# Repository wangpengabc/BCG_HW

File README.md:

<<<<<<< HEAD
# BCG_HW
=======
# BCG_HW
piezo_V1.0 : base electric collector
>>>>>>> f33a43ac3dc7ae816907e558396766c5b4fa1197
nihao

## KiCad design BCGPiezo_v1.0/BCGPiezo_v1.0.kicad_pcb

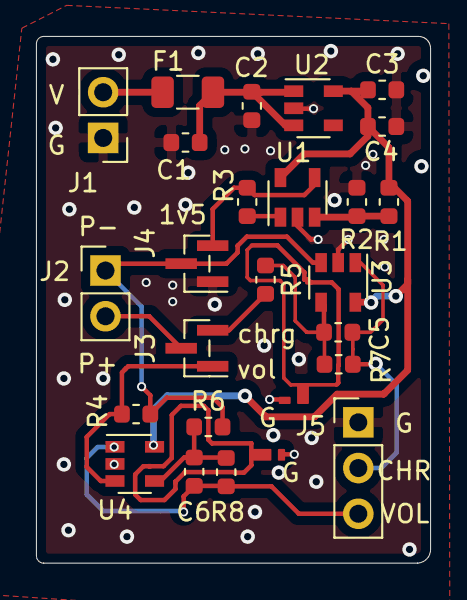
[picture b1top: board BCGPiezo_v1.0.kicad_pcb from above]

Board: 2 copper layers, 21.9 x 29.3 mm, 24 parts (0 on the bottom side), 15 nets.

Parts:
C1, C2, C3: 10uF; C_0603_1608Metric
C4: 0.01uF; C_0603_1608Metric
C5, C6: 10pF; C_0603_1608Metric
F1: Fuse; Fuse_1206_3216Metric
J1, J2: Conn_01x02; PinHeader_1x02_P2.54mm_Vertical
J3, J4: Conn_01x03; PinHeader_1x03_P1.00mm_Vertical_SMD_Pin1Left
J5: Conn_01x03; PinHeader_1x03_P2.54mm_Vertical
R1, R2, R3, R6, R8: 10k; R_0603_1608Metric
R4, R7: 1G; R_0603_1608Metric
R5: R; R_0603_1608Metric
U1, U3, U4: TLV2771; SOT-23-5
U2: LD6836_SOT23; SOT-23-5

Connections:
+1V5: J4.3, R3.1, U1.4
+3V3: C3.1, C4.1, R1.2, U1.5, U2.5, U3.5, U4.5
+BATT: C1.1, C2.1, F1.1, U2.1, U2.3
/charge_out: C5.1, J5.2, R7.1, U3.1
/opmP: J2.1, J4.2, R4.1, R6.2, U3.3
/piezoP: J2.2, J3.2
/vol_mode: J3.1, R4.2, U4.3
/vol_out: C6.1, J5.3, R8.1, U4.1
GND: C1.2, C2.2, C3.2, C4.2, J1.1, J4.1, J5.1, R2.1, U1.2, U2.2, U3.2, U4.2
unnamed: C5.2, R5.1, R7.2, U3.4
unnamed: C6.2, R6.1, R8.2, U4.4
unnamed: F1.2, J1.2
unnamed: J3.3, R5.2
unnamed: R1.1, R2.2, U1.3
unnamed: R3.2, U1.1

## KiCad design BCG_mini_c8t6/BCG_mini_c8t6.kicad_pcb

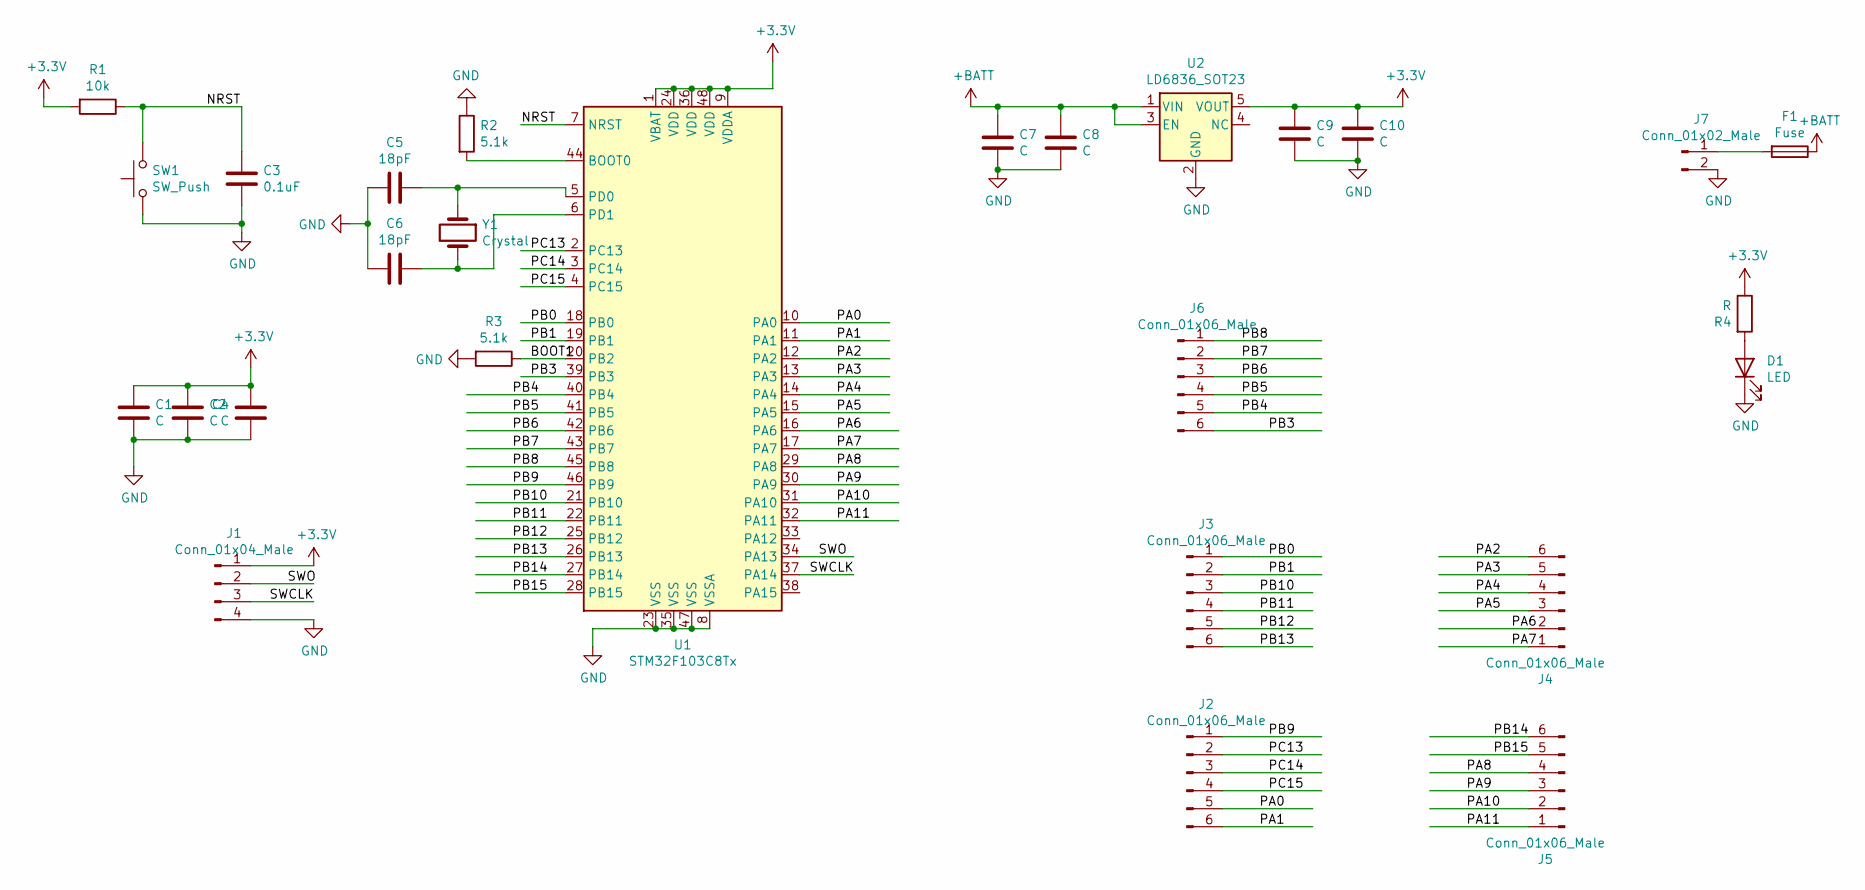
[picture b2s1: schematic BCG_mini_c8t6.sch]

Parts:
C1, C2, C4, C7, C8, C9, C10: C; C_0603_1608Metric
C3: 0.1uF; C_0603_1608Metric
C5, C6: 18pF; C_0603_1608Metric
D1: LED; LED_0603_1608Metric
F1: Fuse; Fuse_0805_2012Metric
J1: Conn_01x04_Male; PinHeader_1x04_P2.54mm_Vertical
J2, J3, J4, J5, J6: Conn_01x06_Male; PinHeader_1x06_P2.54mm_Vertical
J7: Conn_01x02_Male; PinHeader_1x02_P2.54mm_Vertical
R1: 10k; R_0603_1608Metric
R2, R3: 5.1k; R_0603_1608Metric
R4: R; R_0603_1608Metric
SW1: SW_Push; SW_SPST_EVQPE1
U1: STM32F103C8Tx; LQFP-48_7x7mm_P0.5mm
U2: LD6836_SOT23; SOT-23-5
Y1: Crystal; Crystal_SMD_5032-2Pin_5.0x3.2mm

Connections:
+3V3: C1.1, C2.1, C4.2, C9.2, C10.2, J1.1, R1.2, R4.1, U1.1 (VBAT), U1.9 (VDDA), U1.24 (VDD), U1.36 (VDD), U1.48 (VDD), U2.5 (VOUT)
+BATT: C7.2, C8.2, F1.1, U2.1 (VIN), U2.3 (EN)
/BOOT1: R3.1, U1.20 (PB2)
/NRST: C3.1, R1.1, SW1.2, U1.7 (NRST)
/PA0: J2.5, U1.10 (PA0)
/PA1: J2.6, U1.11 (PA1)
/PA2: J4.6, U1.12 (PA2)
/PA3: J4.5, U1.13 (PA3)
/PA4: J4.4, U1.14 (PA4)
/PA5: J4.3, U1.15 (PA5)
/PA6: J4.2, U1.16 (PA6)
/PA7: J4.1, U1.17 (PA7)
/PA8: J5.4, U1.29 (PA8)
/PA9: J5.3, U1.30 (PA9)
/PA10: J5.2, U1.31 (PA10)
/PA11: J5.1, U1.32 (PA11)
/PB0: J3.1, U1.18 (PB0)
/PB1: J3.2, U1.19 (PB1)
/PB3: J6.6, U1.39 (PB3)
/PB4: J6.5, U1.40 (PB4)
/PB5: J6.4, U1.41 (PB5)
/PB6: J6.3, U1.42 (PB6)
/PB7: J6.2, U1.43 (PB7)
/PB8: J6.1, U1.45 (PB8)
/PB9: J2.1, U1.46 (PB9)
/PB10: J3.3, U1.21 (PB10)
/PB11: J3.4, U1.22 (PB11)
/PB12: J3.5, U1.25 (PB12)
/PB13: J3.6, U1.26 (PB13)
/PB14: J5.6, U1.27 (PB14)
/PB15: J5.5, U1.28 (PB15)
/PC13: J2.2, U1.2 (PC13)
/PC14: J2.3, U1.3 (PC14)
/PC15: J2.4, U1.4 (PC15)
/SWCLK: J1.3, U1.37 (PA14)
/SWO: J1.2, U1.34 (PA13)
GND: C1.2, C2.2, C3.2, C4.1, C5.2, C6.2, C7.1, C8.1, C9.1, C10.1, D1.1 (K), J1.4, J7.2, R2.1, R3.2, SW1.1, U1.8 (VSSA), U1.23 (VSS), U1.35 (VSS), U1.47 (VSS), U2.2 (GND)
unnamed: C5.1, U1.5 (PD0), Y1.1
unnamed: C6.1, U1.6 (PD1), Y1.2
unnamed: D1.2 (A), R4.2
unnamed: F1.2, J7.1
unnamed: R2.2, U1.44 (BOOT0)

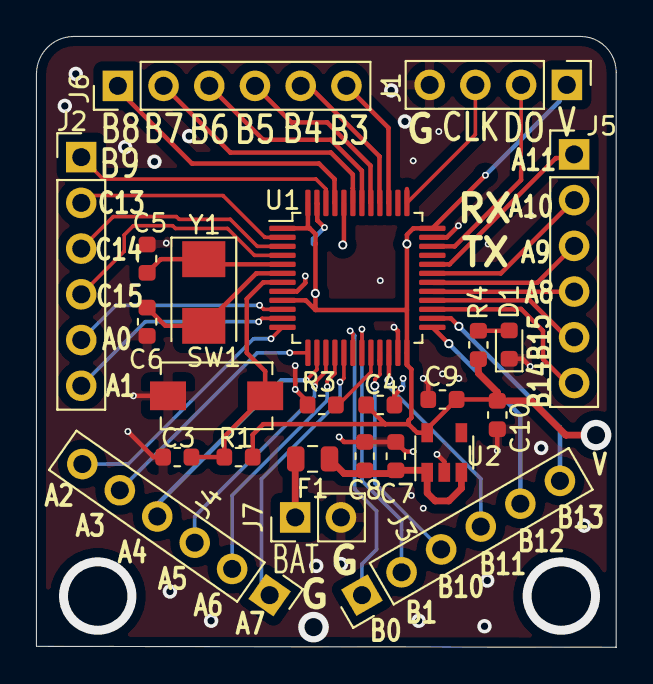
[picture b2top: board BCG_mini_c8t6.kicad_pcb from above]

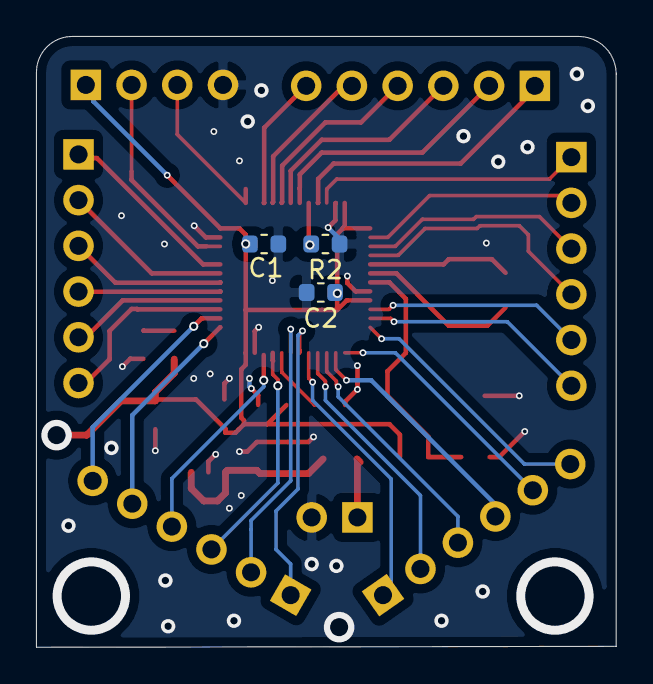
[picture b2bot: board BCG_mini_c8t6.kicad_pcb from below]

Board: 2 copper layers, 32.2 x 33.9 mm, 27 parts (3 on the bottom side), 42 nets.

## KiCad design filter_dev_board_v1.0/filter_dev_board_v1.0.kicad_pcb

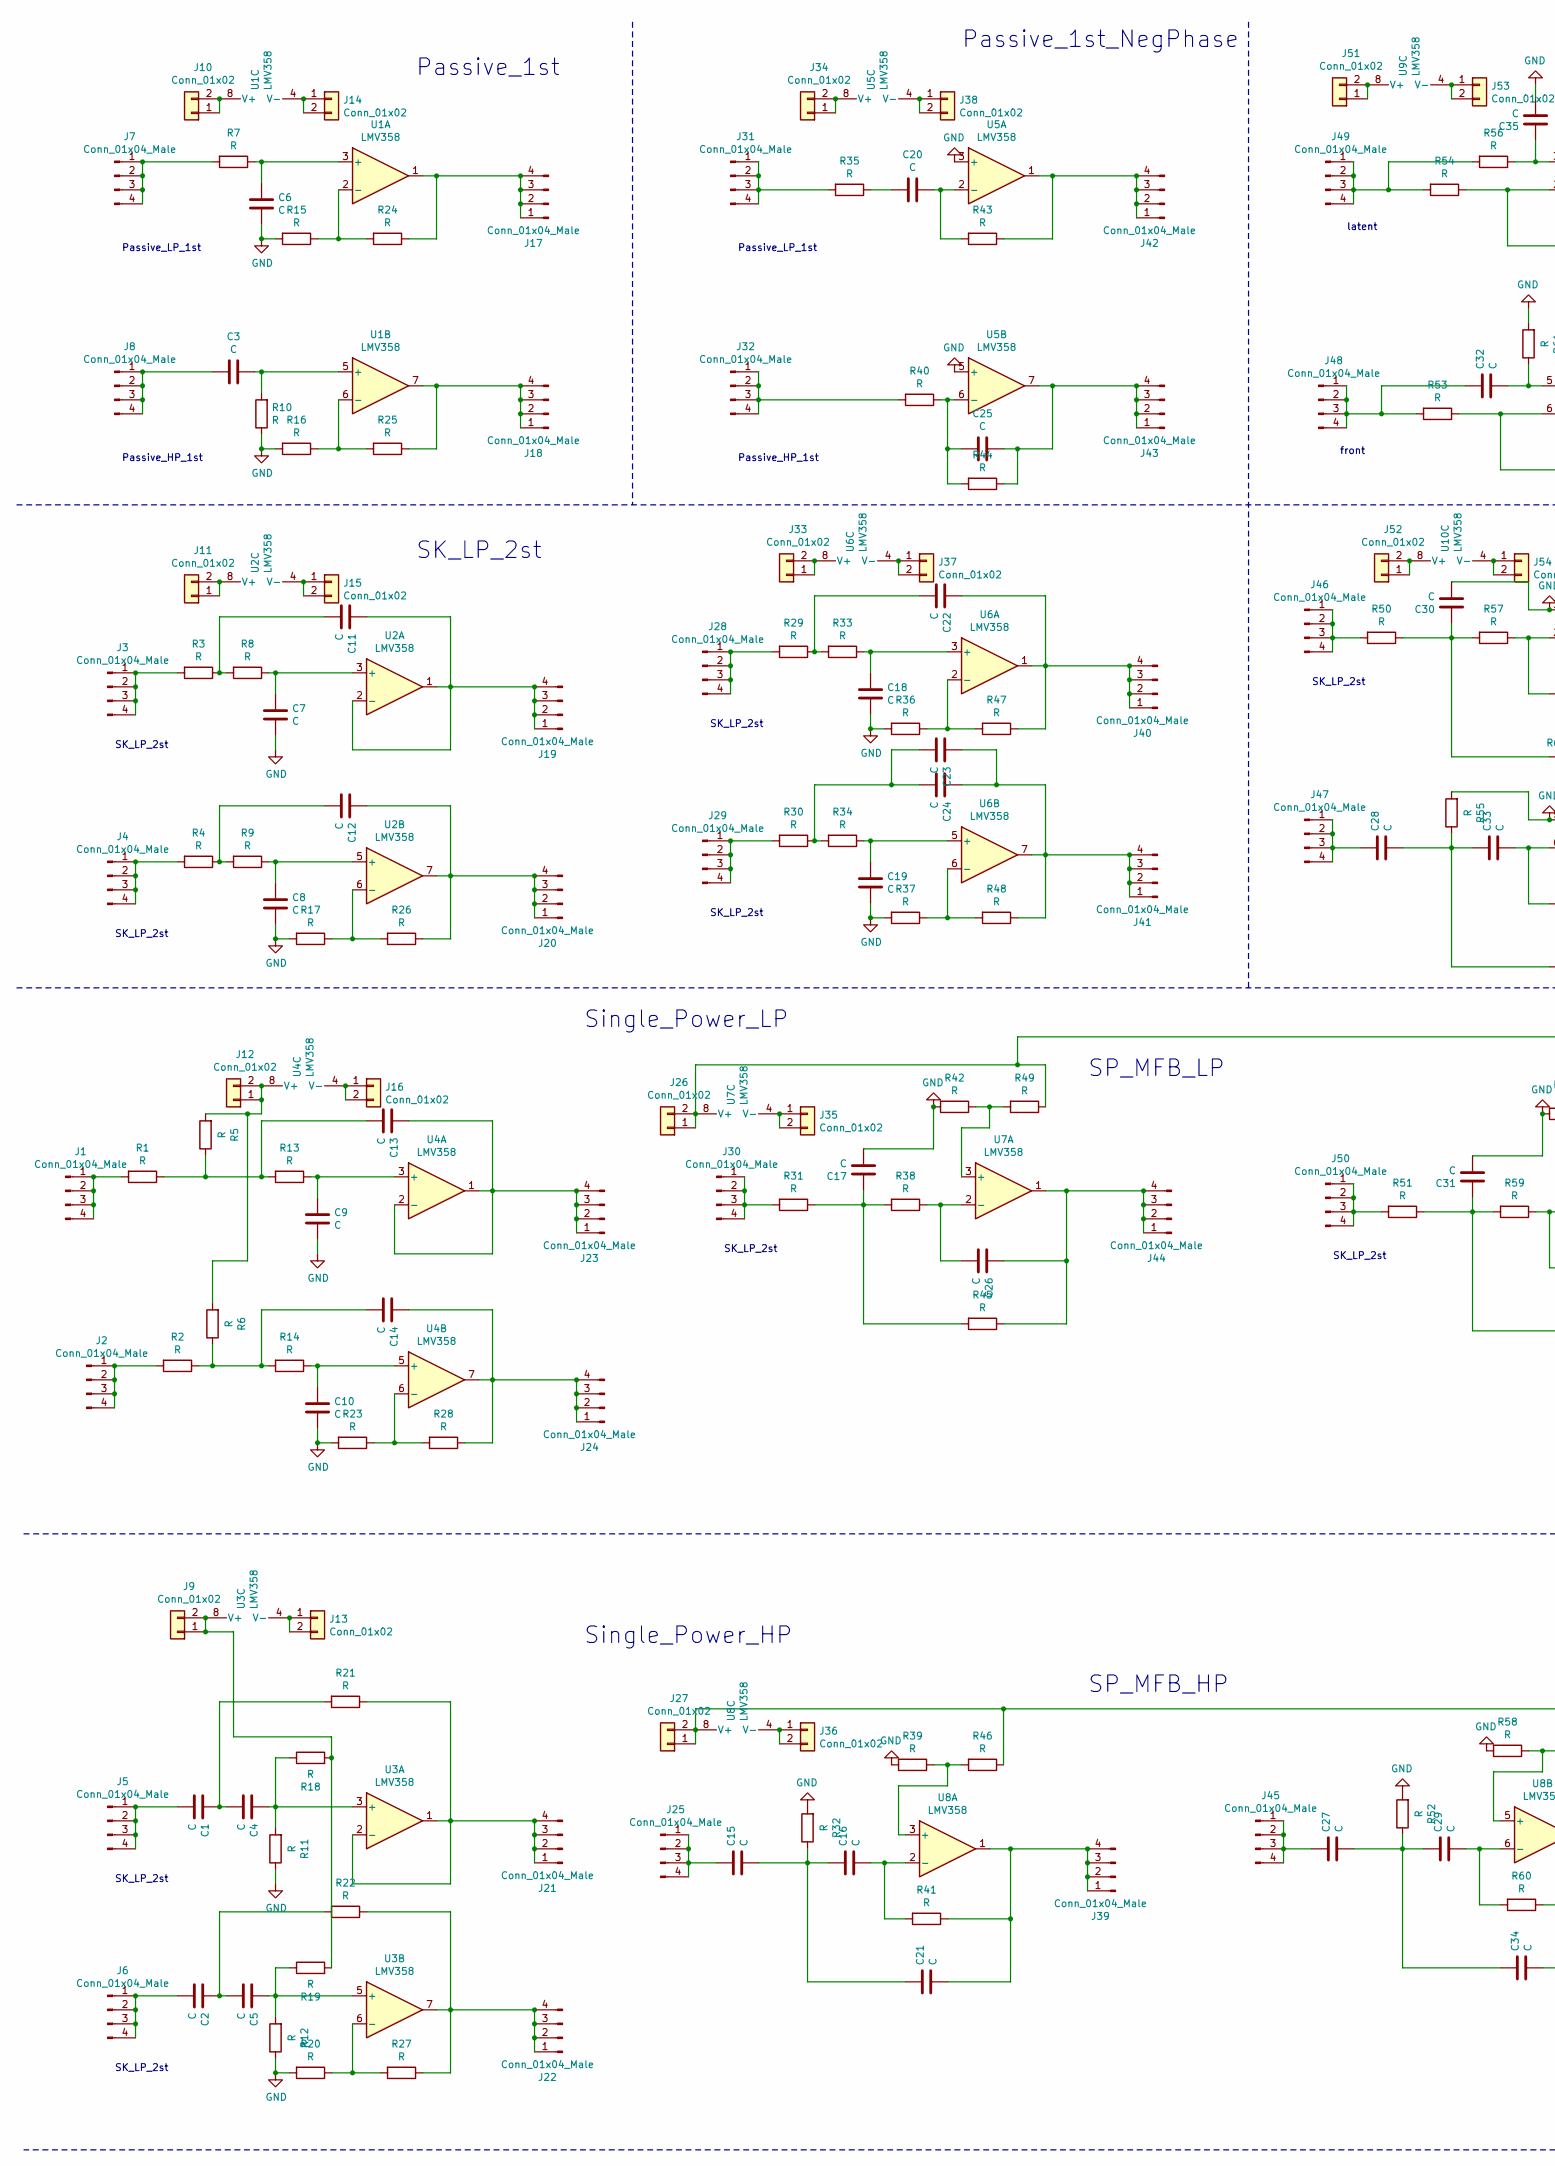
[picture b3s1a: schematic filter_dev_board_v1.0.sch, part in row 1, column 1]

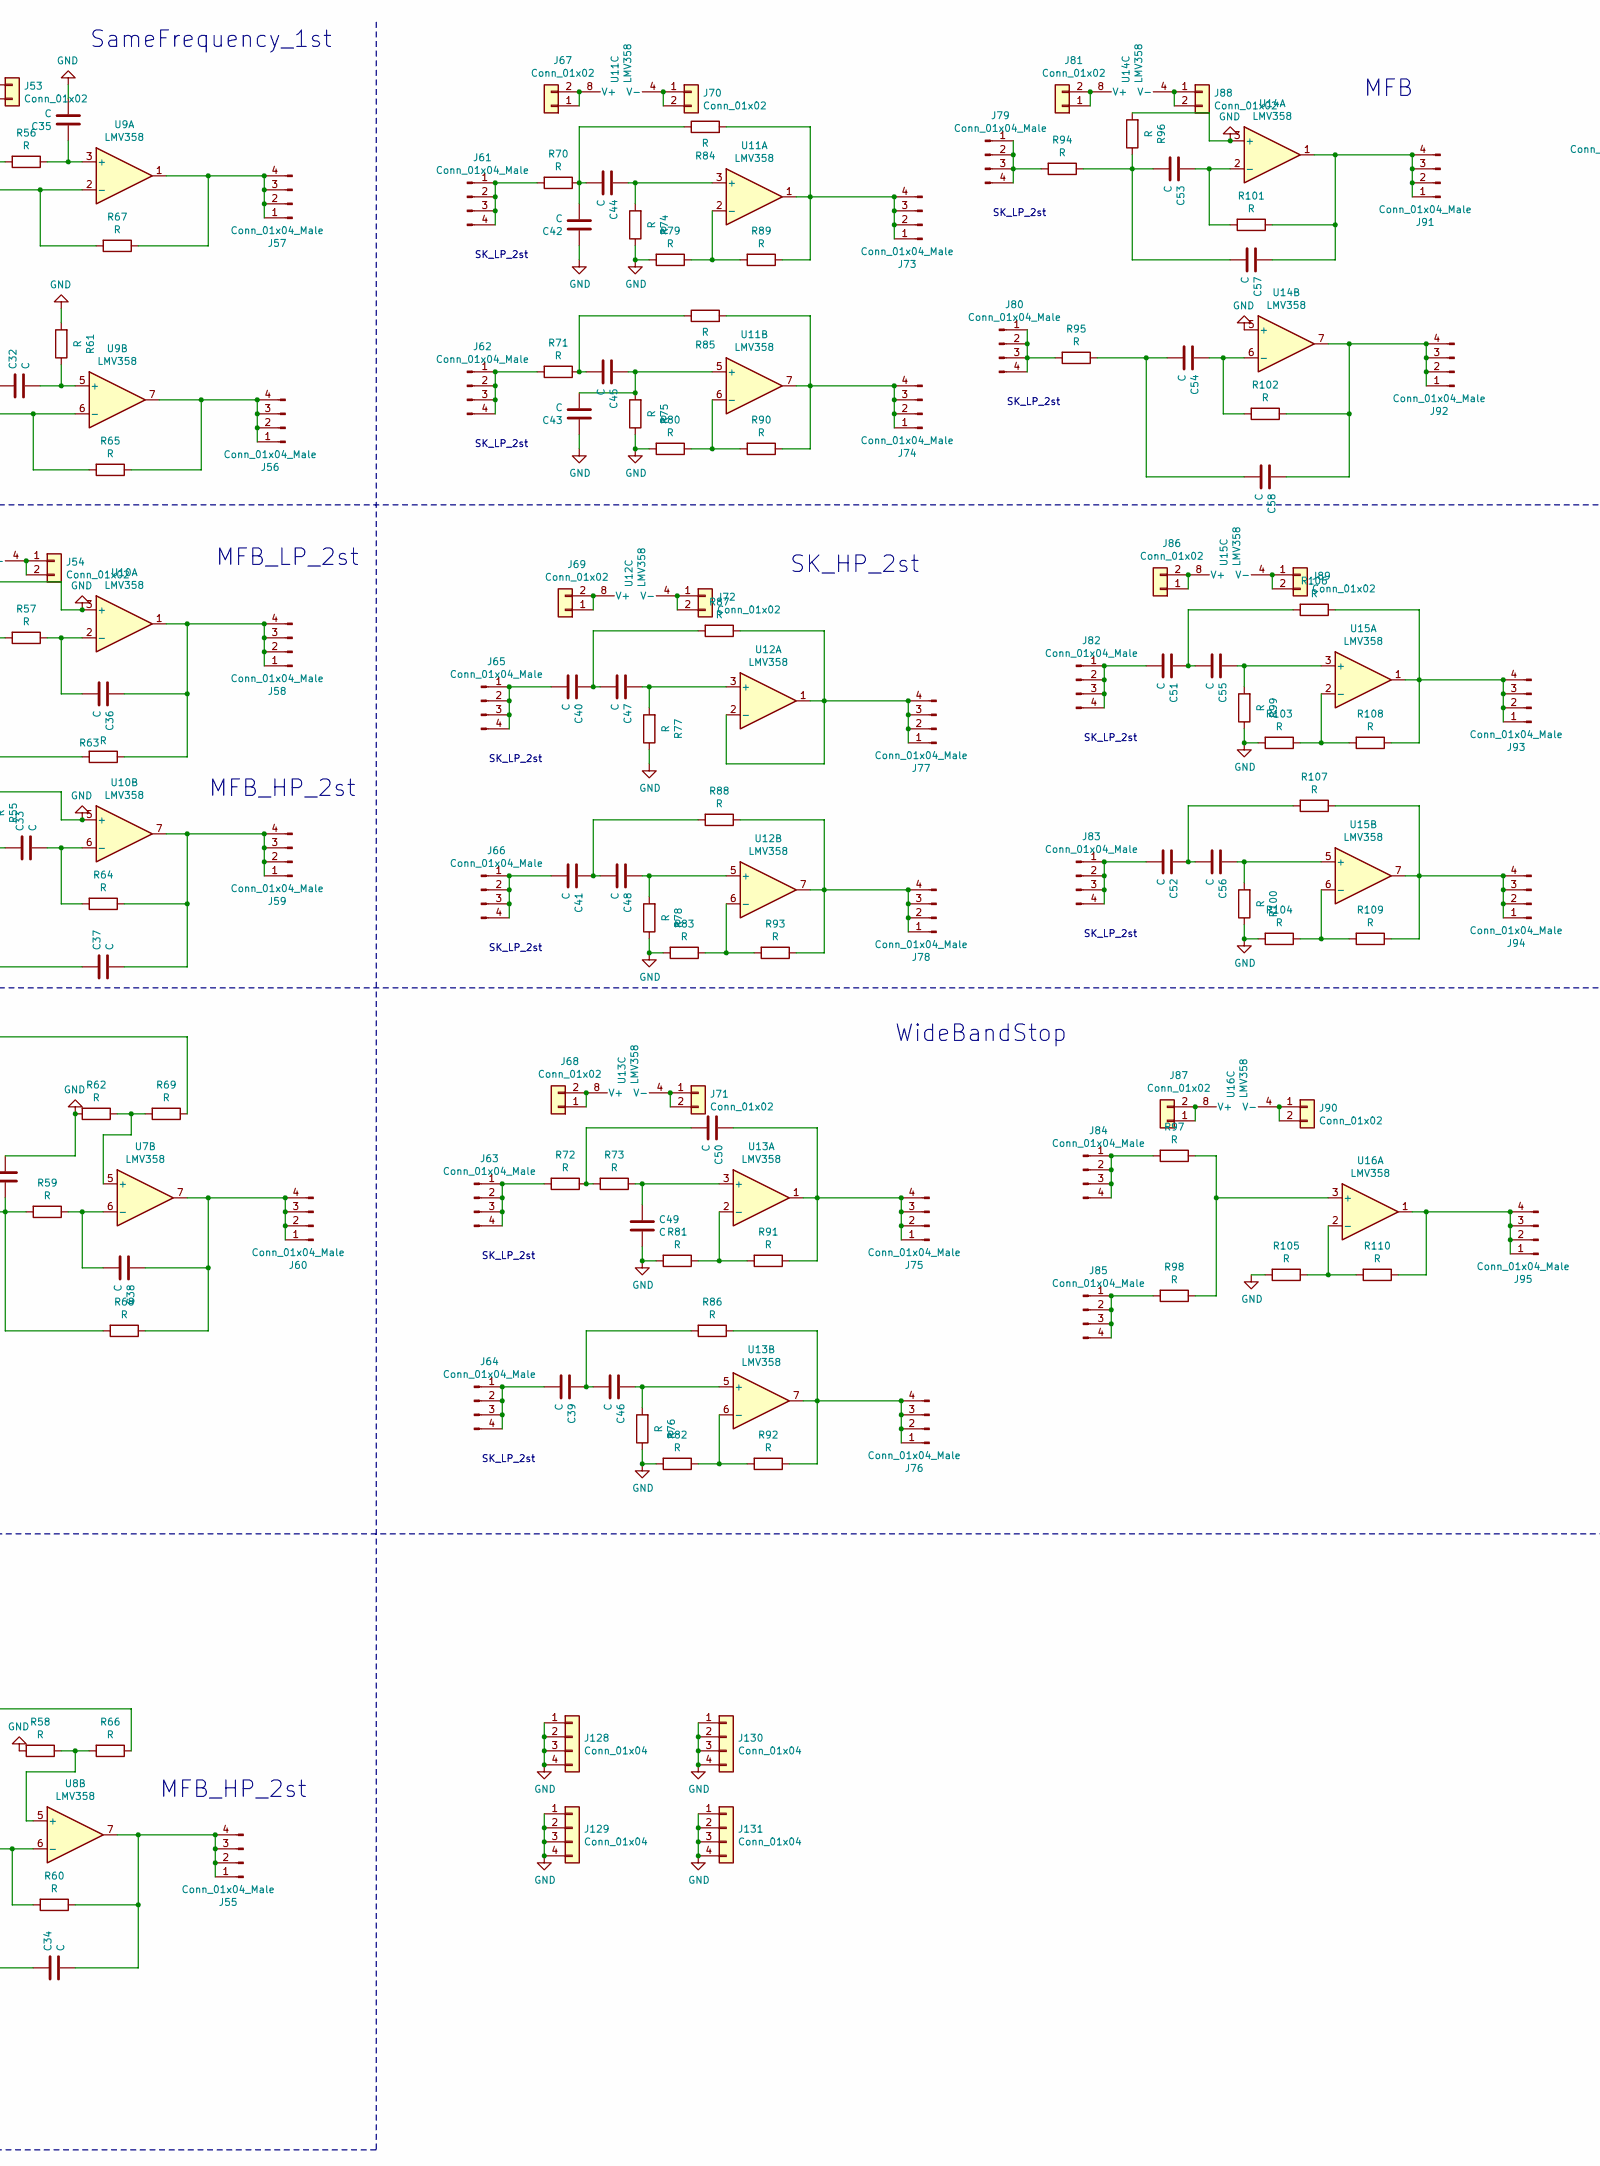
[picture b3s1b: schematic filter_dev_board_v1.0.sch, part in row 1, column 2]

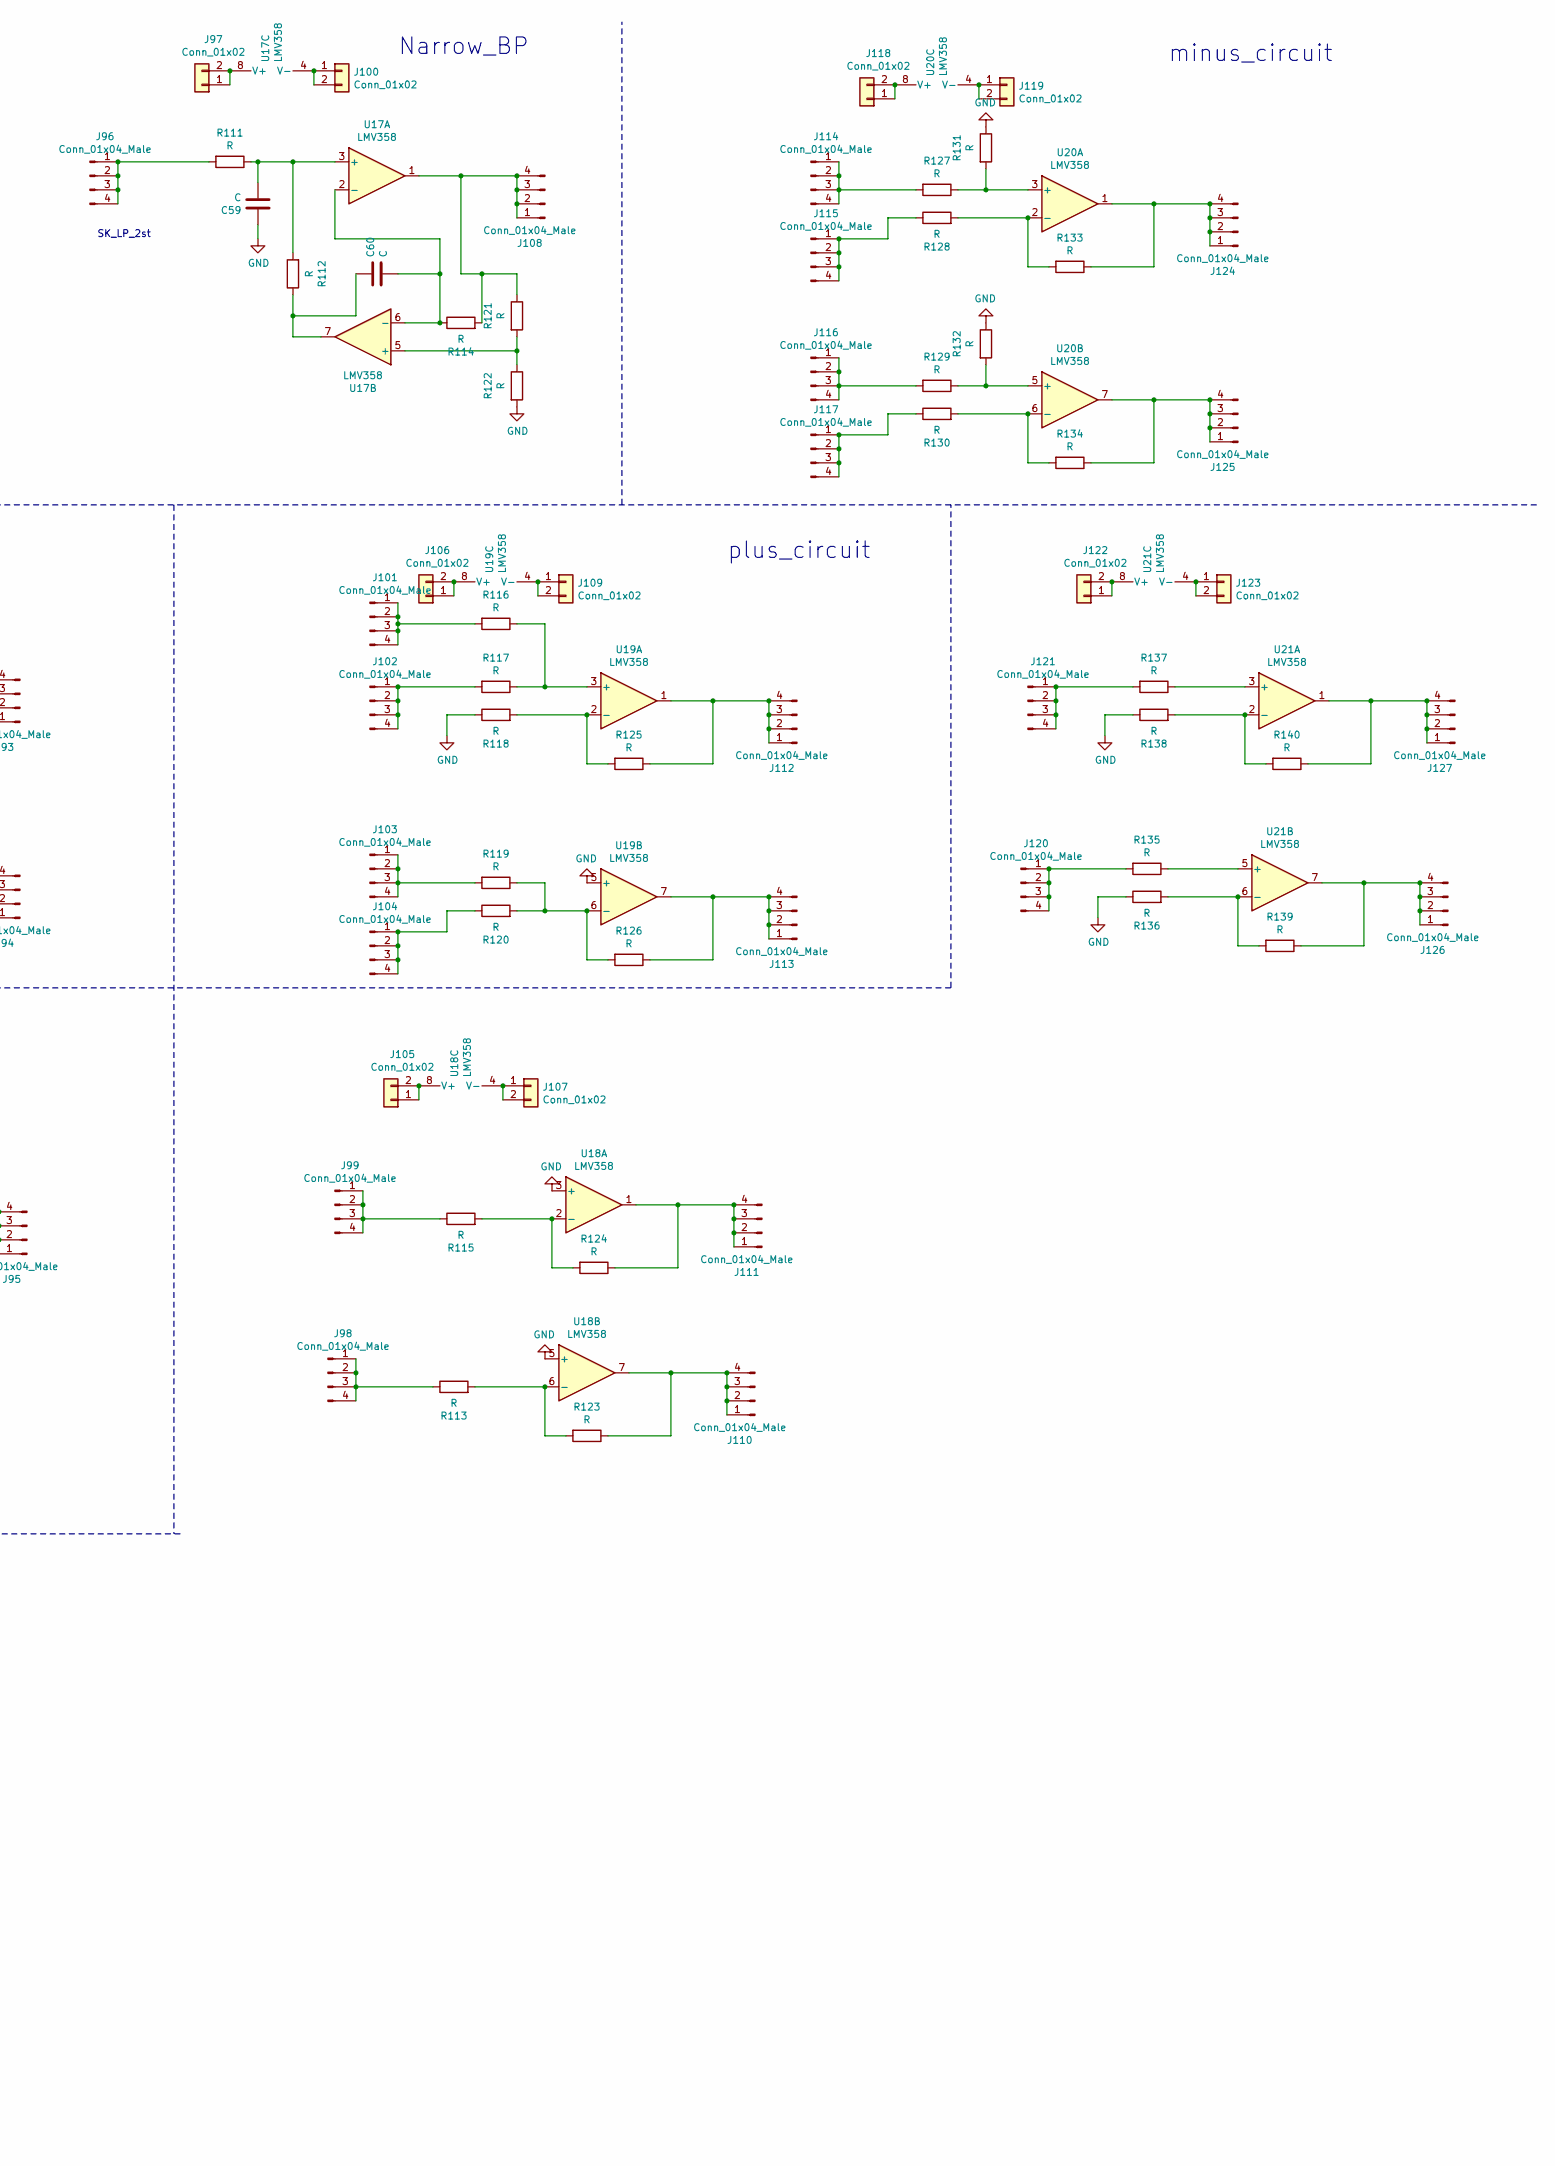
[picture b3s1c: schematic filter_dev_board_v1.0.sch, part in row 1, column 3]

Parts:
C1, C2, C3, C4, C5, C6, C7, C8, C9, C10, C11, C12, C13, C14, C15, C16, C17, C18, C19, C20, C21, C22, C23, C24, C25, C26, C27, C28, C29, C30, C31, C32, C33, C34, C35, C36, C37, C38, C39, C40, C41, C42, C43, C44, C45, C46, C47, C48, C49, C50, C51, C52, C53, C54, C55, C56, C57, C58, C59, C60: C; C_0603_1608Metric
J1, J2, J3, J4, J5, J6, J7, J8, J17, J18, J19, J20, J21, J22, J23, J24, J25, J28, J29, J30, J31, J32, J39, J40, J41, J42, J43, J44, J45, J46, J47, J48, J49, J50, J55, J56, J57, J58, J59, J60, J61, J62, J63, J64, J65, J66, J73, J74, J75, J76, J77, J78, J79, J80, J82, J83, J84, J85, J91, J92, J93, J94, J95, J96, J98, J99, J101, J102, J103, J104, J108, J110, J111, J112, J113, J114, J115, J116, J117, J120, J121, J124, J125, J126, J127: Conn_01x04_Male; PinHeader_1x04_P2.54mm_Vertical
J9, J10, J11, J12, J13, J14, J15, J16, J26, J27, J33, J34, J35, J36, J37, J38, J51, J52, J53, J54, J67, J68, J69, J70, J71, J72, J81, J86, J87, J88, J89, J90, J97, J100, J105, J106, J107, J109, J118, J119, J122, J123: Conn_01x02; PinHeader_1x02_P2.54mm_Vertical
J128, J129, J130, J131: Conn_01x04; PinHeader_1x04_P2.54mm_Vertical
R1, R2, R3, R4, R5, R6, R7, R8, R9, R10, R11, R12, R13, R14, R15, R16, R17, R18, R19, R20, R21, R22, R23, R24, R25, R26, R27, R28, R29, R30, R31, R32, R33, R34, R35, R36, R37, R38, R39, R40, R41, R42, R43, R44, R45, R46, R47, R48, R49, R50, R51, R52, R53, R54, R55, R56, R57, R58, R59, R60, R61, R62, R63, R64, R65, R66, R67, R68, R69, R70, R71, R72, R73, R74, R75, R76, R77, R78, R79, R80, R81, R82, R83, R84, R85, R86, R87, R88, R89, R90, R91, R92, R93, R94, R95, R96, R97, R98, R99, R100, R101, R102, R103, R104, R105, R106, R107, R108, R109, R110, R111, R112, R113, R114, R115, R116, R117, R118, R119, R120, R121, R122, R123, R124, R125, R126, R127, R128, R129, R130, R131, R132, R133, R134, R135, R136, R137, R138, R139, R140: R; R_0603_1608Metric
U1, U2, U3, U4, U5, U6, U7, U8, U9, U10, U11, U12, U13, U14, U15, U16, U17, U18, U19, U20, U21: LMV358; SOP-8_3.9x4.9mm_P1.27mm

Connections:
GND: C6.2, C7.2, C8.2, C9.2, C10.2, C17.2, C18.2, C19.2, C30.2, C31.2, C35.2, C42.1, C43.1, C49.2, C59.1, J128.1, J128.2, J128.3, J128.4, J129.1, J129.2, J129.3, J129.4, J130.1, J130.2, J130.3, J130.4, J131.1, J131.2, J131.3, J131.4, R10.1, R11.1, R12.1, R15.2, R16.2, R17.2, R20.2, R23.2, R32.2, R36.2, R37.2, R39.2, R42.2, R52.2, R55.2, R58.2, R61.2, R62.2, R74.1, R75.1, R76.1, R77.1, R78.1, R79.2, R80.2, R81.2, R82.2, R83.2, R96.2, R99.1, R100.1, R103.2, R104.2, R105.2, R118.1, R122.2, R131.1, R132.1, R136.1, R138.1, U5.3 (+), U5.5 (+), U10.3 (+), U10.5 (+), U14.3 (+), U14.5 (+), U18.3 (+), U18.5 (+), U19.5 (+); also elsewhere on the board
unnamed: C1.1, C4.2, R21.2
unnamed: C1.2, J5.1, J5.2, J5.3, J5.4
unnamed: C2.1, C5.2, R22.2
unnamed: C2.2, J6.1, J6.2, J6.3, J6.4
unnamed: C3.1, R10.2, U1.5 (+)
unnamed: C3.2, J8.1, J8.2, J8.3, J8.4
unnamed: C4.1, R11.2, R18.1, U3.3 (+)
unnamed: C5.1, R12.2, R19.1, U3.5 (+)
unnamed: C6.1, R7.1, U1.3 (+)
unnamed: C7.1, R8.1, U2.3 (+)
unnamed: C8.1, R9.1, U2.5 (+)
unnamed: C9.1, R13.1, U4.3 (+)
unnamed: C10.1, R14.1, U4.5 (+)
unnamed: C11.1, J19.1, J19.2, J19.3, J19.4, U2.1, U2.2 (-)
unnamed: C11.2, R3.1, R8.2
unnamed: C12.1, J20.1, J20.2, J20.3, J20.4, R26.1, U2.7
unnamed: C12.2, R4.1, R9.2
unnamed: C13.1, J23.1, J23.2, J23.3, J23.4, U4.1, U4.2 (-)
unnamed: C13.2, R1.1, R5.1, R13.2
unnamed: C14.1, J24.1, J24.2, J24.3, J24.4, R28.1, U4.7
unnamed: C14.2, R2.1, R6.1, R14.2
unnamed: C15.1, J25.1, J25.2, J25.3, J25.4
unnamed: C15.2, C16.1, C21.1, R32.1
unnamed: C16.2, R41.2, U8.2 (-)
unnamed: C17.1, R31.1, R38.2, R45.2
unnamed: C18.1, R33.1, U6.3 (+)
unnamed: C19.1, R34.1, U6.5 (+)
unnamed: C20.1, R43.2, U5.2 (-)
unnamed: C20.2, R35.1
unnamed: C21.2, J39.1, J39.2, J39.3, J39.4, R41.1, U8.1
unnamed: C22.1, J40.1, J40.2, J40.3, J40.4, R47.1, U6.1
unnamed: C22.2, R29.1, R33.2
unnamed: C23.1, C24.1, J41.1, J41.2, J41.3, J41.4, R48.1, U6.7
unnamed: C23.2, C24.2, R30.1, R34.2
unnamed: C25.1, J43.1, J43.2, J43.3, J43.4, R44.1, U5.7
unnamed: C25.2, R40.1, R44.2, U5.6 (-)
unnamed: C26.1, J44.1, J44.2, J44.3, J44.4, R45.1, U7.1
unnamed: C26.2, R38.1, U7.2 (-)
unnamed: C27.1, J45.1, J45.2, J45.3, J45.4
unnamed: C27.2, C29.1, C34.1, R52.1
unnamed: C28.1, J47.1, J47.2, J47.3, J47.4
unnamed: C28.2, C33.1, C37.1, R55.1
unnamed: C29.2, R60.2, U8.6 (-)
unnamed: C30.1, R50.1, R57.2, R63.2
unnamed: C31.1, R51.1, R59.2, R68.2
unnamed: C32.1, J48.1, J48.2, J48.3, J48.4, R53.2
unnamed: C32.2, R61.1, U9.5 (+)
unnamed: C33.2, R64.2, U10.6 (-)
unnamed: C34.2, J55.1, J55.2, J55.3, J55.4, R60.1, U8.7
unnamed: C35.1, R56.1, U9.3 (+)
unnamed: C36.1, J58.1, J58.2, J58.3, J58.4, R63.1, U10.1
unnamed: C36.2, R57.1, U10.2 (-)
unnamed: C37.2, J59.1, J59.2, J59.3, J59.4, R64.1, U10.7
unnamed: C38.1, J60.1, J60.2, J60.3, J60.4, R68.1, U7.7
unnamed: C38.2, R59.1, U7.6 (-)
unnamed: C39.1, C46.2, R86.2
unnamed: C39.2, J64.1, J64.2, J64.3, J64.4
unnamed: C40.1, C47.2, R87.2
unnamed: C40.2, J65.1, J65.2, J65.3, J65.4
unnamed: C41.1, C48.2, R88.2
unnamed: C41.2, J66.1, J66.2, J66.3, J66.4
unnamed: C42.2, C44.2, R70.1, R84.1
unnamed: C43.2, C45.1, R75.2, U11.5 (+)
unnamed: C44.1, R74.2, U11.3 (+)
unnamed: C45.2, R71.1, R85.1
unnamed: C46.1, R76.2, U13.5 (+)
unnamed: C47.1, R77.2, U12.3 (+)
unnamed: C48.1, R78.2, U12.5 (+)
unnamed: C49.1, R73.1, U13.3 (+)
unnamed: C50.1, J75.1, J75.2, J75.3, J75.4, R91.1, U13.1
unnamed: C50.2, R72.1, R73.2
unnamed: C51.1, C55.2, R106.2
unnamed: C51.2, J82.1, J82.2, J82.3, J82.4
unnamed: C52.1, C56.2, R107.2
unnamed: C52.2, J83.1, J83.2, J83.3, J83.4
unnamed: C53.1, R101.2, U14.2 (-)
unnamed: C53.2, C57.2, R94.1, R96.1
unnamed: C54.1, R102.2, U14.6 (-)
unnamed: C54.2, C58.2, R95.1
unnamed: C55.1, R99.2, U15.3 (+)
unnamed: C56.1, R100.2, U15.5 (+)
unnamed: C57.1, J91.1, J91.2, J91.3, J91.4, R101.1, U14.1
unnamed: C58.1, J92.1, J92.2, J92.3, J92.4, R102.1, U14.7
unnamed: C59.2, R111.1, R112.2, U17.3 (+)
unnamed: C60.1, R112.1, U17.7
unnamed: C60.2, R114.1, U17.2 (-), U17.6 (-)
unnamed: J1.1, J1.2, J1.3, J1.4, R1.2
unnamed: J2.1, J2.2, J2.3, J2.4, R2.2
unnamed: J3.1, J3.2, J3.3, J3.4, R3.2
unnamed: J4.1, J4.2, J4.3, J4.4, R4.2
unnamed: J7.1, J7.2, J7.3, J7.4, R7.2
unnamed: J9.1, J9.2, R18.2, R19.2, U3.8 (V+)
unnamed: J10.1, J10.2, U1.8 (V+)
unnamed: J11.1, J11.2, U2.8 (V+)
unnamed: J12.1, J12.2, R5.2, R6.2, U4.8 (V+)
unnamed: J13.1, J13.2, U3.4 (V-)
unnamed: J14.1, J14.2, U1.4 (V-)
unnamed: J15.1, J15.2, U2.4 (V-)
unnamed: J16.1, J16.2, U4.4 (V-)
unnamed: J17.1, J17.2, J17.3, J17.4, R24.1, U1.1
unnamed: J18.1, J18.2, J18.3, J18.4, R25.1, U1.7
unnamed: J21.1, J21.2, J21.3, J21.4, R21.1, U3.1, U3.2 (-)
unnamed: J22.1, J22.2, J22.3, J22.4, R22.1, R27.1, U3.7
unnamed: J26.1, J26.2, R49.1, R69.1, U7.8 (V+)
unnamed: J27.1, J27.2, R46.1, R66.1, U8.8 (V+)
unnamed: J28.1, J28.2, J28.3, J28.4, R29.2
unnamed: J29.1, J29.2, J29.3, J29.4, R30.2
unnamed: J30.1, J30.2, J30.3, J30.4, R31.2
unnamed: J31.1, J31.2, J31.3, J31.4, R35.2
unnamed: J32.1, J32.2, J32.3, J32.4, R40.2
unnamed: J33.1, J33.2, U6.8 (V+)
unnamed: J34.1, J34.2, U5.8 (V+)
unnamed: J35.1, J35.2, U7.4 (V-)
unnamed: J36.1, J36.2, U8.4 (V-)
unnamed: J37.1, J37.2, U6.4 (V-)
unnamed: J38.1, J38.2, U5.4 (V-)
unnamed: J42.1, J42.2, J42.3, J42.4, R43.1, U5.1
unnamed: J46.1, J46.2, J46.3, J46.4, R50.2
unnamed: J49.1, J49.2, J49.3, J49.4, R54.2, R56.2
unnamed: J50.1, J50.2, J50.3, J50.4, R51.2
unnamed: J51.1, J51.2, U9.8 (V+)
unnamed: J52.1, J52.2, U10.8 (V+)
unnamed: J53.1, J53.2, U9.4 (V-)
unnamed: J54.1, J54.2, U10.4 (V-)
unnamed: J56.1, J56.2, J56.3, J56.4, R65.1, U9.7
unnamed: J57.1, J57.2, J57.3, J57.4, R67.1, U9.1
unnamed: J61.1, J61.2, J61.3, J61.4, R70.2
unnamed: J62.1, J62.2, J62.3, J62.4, R71.2
unnamed: J63.1, J63.2, J63.3, J63.4, R72.2
unnamed: J67.1, J67.2, U11.8 (V+)
unnamed: J68.1, J68.2, U13.8 (V+)
unnamed: J69.1, J69.2, U12.8 (V+)
unnamed: J70.1, J70.2, U11.4 (V-)
unnamed: J71.1, J71.2, U13.4 (V-)
unnamed: J72.1, J72.2, U12.4 (V-)
unnamed: J73.1, J73.2, J73.3, J73.4, R84.2, R89.1, U11.1
unnamed: J74.1, J74.2, J74.3, J74.4, R85.2, R90.1, U11.7
unnamed: J76.1, J76.2, J76.3, J76.4, R86.1, R92.1, U13.7
unnamed: J77.1, J77.2, J77.3, J77.4, R87.1, U12.1, U12.2 (-)
unnamed: J78.1, J78.2, J78.3, J78.4, R88.1, R93.1, U12.7
unnamed: J79.1, J79.2, J79.3, J79.4, R94.2
unnamed: J80.1, J80.2, J80.3, J80.4, R95.2
unnamed: J81.1, J81.2, U14.8 (V+)
unnamed: J84.1, J84.2, J84.3, J84.4, R97.2
unnamed: J85.1, J85.2, J85.3, J85.4, R98.2
unnamed: J86.1, J86.2, U15.8 (V+)
unnamed: J87.1, J87.2, U16.8 (V+)
unnamed: J88.1, J88.2, U14.4 (V-)
unnamed: J89.1, J89.2, U15.4 (V-)
unnamed: J90.1, J90.2, U16.4 (V-)
unnamed: J93.1, J93.2, J93.3, J93.4, R106.1, R108.1, U15.1
unnamed: J94.1, J94.2, J94.3, J94.4, R107.1, R109.1, U15.7
unnamed: J95.1, J95.2, J95.3, J95.4, R110.1, U16.1
unnamed: J96.1, J96.2, J96.3, J96.4, R111.2
unnamed: J97.1, J97.2, U17.8 (V+)
unnamed: J98.1, J98.2, J98.3, J98.4, R113.1
unnamed: J99.1, J99.2, J99.3, J99.4, R115.1
unnamed: J100.1, J100.2, U17.4 (V-)
unnamed: J101.1, J101.2, J101.3, J101.4, R116.2
unnamed: J102.1, J102.2, J102.3, J102.4, R117.2
unnamed: J103.1, J103.2, J103.3, J103.4, R119.2
unnamed: J104.1, J104.2, J104.3, J104.4, R120.1
unnamed: J105.1, J105.2, U18.8 (V+)
unnamed: J106.1, J106.2, U19.8 (V+)
unnamed: J107.1, J107.2, U18.4 (V-)
unnamed: J108.1, J108.2, J108.3, J108.4, R114.2, R121.1, U17.1
unnamed: J109.1, J109.2, U19.4 (V-)
unnamed: J110.1, J110.2, J110.3, J110.4, R123.1, U18.7
unnamed: J111.1, J111.2, J111.3, J111.4, R124.1, U18.1
unnamed: J112.1, J112.2, J112.3, J112.4, R125.1, U19.1
unnamed: J113.1, J113.2, J113.3, J113.4, R126.1, U19.7
unnamed: J114.1, J114.2, J114.3, J114.4, R127.2
unnamed: J115.1, J115.2, J115.3, J115.4, R128.1
unnamed: J116.1, J116.2, J116.3, J116.4, R129.2
unnamed: J117.1, J117.2, J117.3, J117.4, R130.1
unnamed: J118.1, J118.2, U20.8 (V+)
unnamed: J119.1, J119.2, U20.4 (V-)
unnamed: J120.1, J120.2, J120.3, J120.4, R135.2
unnamed: J121.1, J121.2, J121.3, J121.4, R137.2
unnamed: J122.1, J122.2, U21.8 (V+)
unnamed: J123.1, J123.2, U21.4 (V-)
unnamed: J124.1, J124.2, J124.3, J124.4, R133.1, U20.1
unnamed: J125.1, J125.2, J125.3, J125.4, R134.1, U20.7
unnamed: J126.1, J126.2, J126.3, J126.4, R139.1, U21.7
unnamed: J127.1, J127.2, J127.3, J127.4, R140.1, U21.1
unnamed: R15.1, R24.2, U1.2 (-)
unnamed: R16.1, R25.2, U1.6 (-)
unnamed: R17.1, R26.2, U2.6 (-)
unnamed: R20.1, R27.2, U3.6 (-)
unnamed: R23.1, R28.2, U4.6 (-)
unnamed: R36.1, R47.2, U6.2 (-)
unnamed: R37.1, R48.2, U6.6 (-)
unnamed: R39.1, R46.2, U8.3 (+)
unnamed: R42.1, R49.2, U7.3 (+)
unnamed: R53.1, R65.2, U9.6 (-)
unnamed: R54.1, R67.2, U9.2 (-)
unnamed: R58.1, R66.2, U8.5 (+)
unnamed: R62.1, R69.2, U7.5 (+)
unnamed: R79.1, R89.2, U11.2 (-)
unnamed: R80.1, R90.2, U11.6 (-)
unnamed: R81.1, R91.2, U13.2 (-)
unnamed: R82.1, R92.2, U13.6 (-)
unnamed: R83.1, R93.2, U12.6 (-)
unnamed: R97.1, R98.1, U16.3 (+)
unnamed: R103.1, R108.2, U15.2 (-)
unnamed: R104.1, R109.2, U15.6 (-)
unnamed: R105.1, R110.2, U16.2 (-)
unnamed: R113.2, R123.2, U18.6 (-)
unnamed: R115.2, R124.2, U18.2 (-)
unnamed: R116.1, R117.1, U19.3 (+)
unnamed: R118.2, R125.2, U19.2 (-)
unnamed: R119.1, R120.2, R126.2, U19.6 (-)
unnamed: R121.2, R122.1, U17.5 (+)
unnamed: R127.1, R131.2, U20.3 (+)
unnamed: R128.2, R133.2, U20.2 (-)
unnamed: R129.1, R132.2, U20.5 (+)
unnamed: R130.2, R134.2, U20.6 (-)
unnamed: R135.1, U21.5 (+)
unnamed: R136.2, R139.2, U21.6 (-)
unnamed: R137.1, U21.3 (+)
unnamed: R138.2, R140.2, U21.2 (-)

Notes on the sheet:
Passive_LP_1st
Passive_HP_1st
Passive_1st
Passive_1st_NegPhase
SameFrequency_1st
latent
front
SK_LP_2st
SK_LP_2st
MFB_LP_2st
Single_Power_LP
SP_MFB_LP
SK_HP_2st
MFB_HP_2st
Single_Power_HP
SP_MFB_HP
WideBandStop
Narrow_BP
MFB
minus_circuit
plus_circuit
